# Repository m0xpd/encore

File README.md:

# encore!
An Echo/Delay Module for Eurorack, based on the PT2399

This repository describes a delay module, developed for electronic synthesisers, in Eurorack format, based on the [Princeton Technology](http://www.princeton.com.tw/en-us/products.aspx) [PT2399](http://www.princeton.com.tw/LinkClick.aspx?fileticket=XG0VYKi9QxE%3d&tabid=341&portalid=0&mid=828&language=en-US) device. 

**Functional Description**

A block diagram of  encore!  is shown below:

The module uses the PT2399 in an application environment derived from circuits in the [datasheet](http://www.princeton.com.tw/LinkClick.aspx?fileticket=XG0VYKi9QxE%3d&tabid=341&portalid=0&mid=828&language=en-US), but adds resources to enable patching and use in the Eurorack environment. 
These resources are described below.

In addition to the filtering already suggested in the application circuit and supported by the PT2399's integral amplifiers, encore! adds a 2nd order 
input filter and a 4th order output filter in Butterworth configuration. 

Unlike most simple PT2399 delay circuits, which are adjusted by potentiometers, encore! places the key parameters of Delay Length, Repeats (i.e. the gain 
of the recursion/feedback loop) and Level of the 'Wet' signal under voltage control, allowing parameter adjustment by potentiometers and/or CV inputs. 

In the case of the Delay Length, this is achieved by a Voltage Controlled Resistor circuit. 

In the case of the other two parameters, this is achieved by Voltage Controlled Amplifiers.  

Most significantly, encore! allows the user to patch external functions into the feedback/recursion loop that builds the echo (seen in the red dashed box in 
the block diagram above), using a loop send / return feature, which is mixed with the module's internal feedback path. This allows (e.g.) filters to be inserted 
to allow selective echos, multiple delay units to be cross-patched to build up complex echo strutures, etc..

**Licensing**

encore! is published under a Creative Commons BY-SA 4.0 [License](https://github.com/m0xpd/encore/blob/main/LICENSE.txt)

**Implementation**

The system is implemented on two PCBs; one for the main electronics and one for the controls and interface components.

The schematic for the main PCB is linked by the graphic below below (click for the full-size schematic):

I should have put a buffer between the PT2399 output filters and the input to the 'output filter' (which doesn't have a very high input impedance), but I 
didn't have any spare op-amp stages. I can live with the loading interactions as they are!

The schematic for the control PCB is linked below:

The two PCBs are joined electrically and mechanically by the 'Board interface', implemented as two 20-way headers (JP1 and JP2 in the schematics, male on the
 main board and female on the control board). A BoM for the main board is included.

You will find full details of the two printed circuit boards (in files for the Eagle Layout Editor) [here](https://github.com/m0xpd/encore/tree/main/PCBs) and 
a Kicad project defining a front panel [here](https://github.com/m0xpd/encore/tree/main/FrontPanel).

**Specifications**

encore! is 12HP wide and extends 38mm behind the front panel (when a standard Eurorack power header is inserted).

Caution: I've just been reminded (thanks Alex) that the PCBs of the present design overhang the left hand edge of the front panel by approximately 1mm. This 
is **an error on my part**, which I'll correct if ever there's a new 'edition' of encore! Multiple instances of encore! sit next to each other in a rack with 
no worries, but don't try to sit encore! next to a neighbour on its left which doesn't leave sufficient space.

encore! draws 36.5 mA from the +12V rail, 12.5 mA from the -12V rail, and nothing from the 5V rail.

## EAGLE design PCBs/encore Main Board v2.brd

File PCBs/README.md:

# Printed Circuit Boards

This folder contains details of the two PCBs required to implement the encore! delay module.

The PCB design files are presented in Eagle format.

Below you see a photo of the unpopulated PCBs.

The photo shows (left to right) the Main Board Component Side (Top), Main Board Bottom, Control Board Component Side (Top), and Control Board Bottom. 

Images of the main board on this repository are currently of a v1 protoype which included an error (a missing resistor), which is corrected in the design files.

## Main Board Capacitors 

The [BoM](https://github.com/m0xpd/encore/blob/main/PCBs/encore%20Main%20Board%20v2%20BoM.txt) is presented in the standard EAGLE format, which is verbose and not always helpful. A description of the capacitors used on the main board is given 
below (refer to the [schematic](https://user-images.githubusercontent.com/3152962/246648781-e0986f40-e248-4756-a811-1461d0e43b70.png) for component idents).

De-coupling capacitors C1, C2, C12, C13, C9, C20, C21 and modulate/de-modulate capacitors for the PT2399, C23, C24, C30, C32 (all having value quoted as 
“0.1u” in the BoM) are disc ceramics with 0.2-inch pitch.

Filter / coupling capacitors (C5, C7, C8, C14, C15, C16, C17, C18, C19, C25, C27, C28, C31, C33) are ceramics (for pF values), or multi-layer ceramics 
(for nF values), most of which have 0.1-inch pitch (except C7, C9, C27 & C33, where I used 0.2-inch pitch components for my own convenience). 

Polarized capacitors with 0.1-inch pitch are used for power supply smoothing (C3, C4, C10, C11), smoothing the mid-rail voltage of the PT2399 (C22) and 
d.c. blocking (C26, C29).

There is NO C6, due to an indexing error on my part.

## Control Board Components

Certain components on the control board have mechanical as well as electrical significance.

VR2 VR3 and VR4 are 9mm Vertical Alpha potentiometers [such as these](https://www.thonk.co.uk/shop/alpha-9mm-pots-vertical-t18/)

SK1:SK10 are [Thonkiconn](https://www.thonk.co.uk/shop/thonkiconn/) 3.5mm jack sockets

The combination of the alpha potentiometers and the Thonkiconn jacks gives the correct spacing between the Control Board and the Front Panel.

VR1 and VR5 are Song Huei 9mm Trim Pots, such as [these](https://www.thonk.co.uk/shop/ttpots/)

## Control Board 5V Power

5V is required on the Control Board for the derivation of control voltages via VR2:4 and the limiting of externally applied CVs via the Schottky diodes D1:6.

I did not want to use the PT2399's 5V supply in this application and found it convenient to generate 5V using a 78L05 regulator ("IC1") from the 12V rail, 
even though a much simpler circuit could have been used. Laziness rules! 

## Board Interface

Electrical and Mechanical Interface between the Main and Control Boards is achieved using 20-way 0.1-inch headers (JP1 & JP2). These are preferably a 
male component on the Main Board and a female component on the Control Board. I find it convenient to buy packs of 40-way headers and cut down to size.

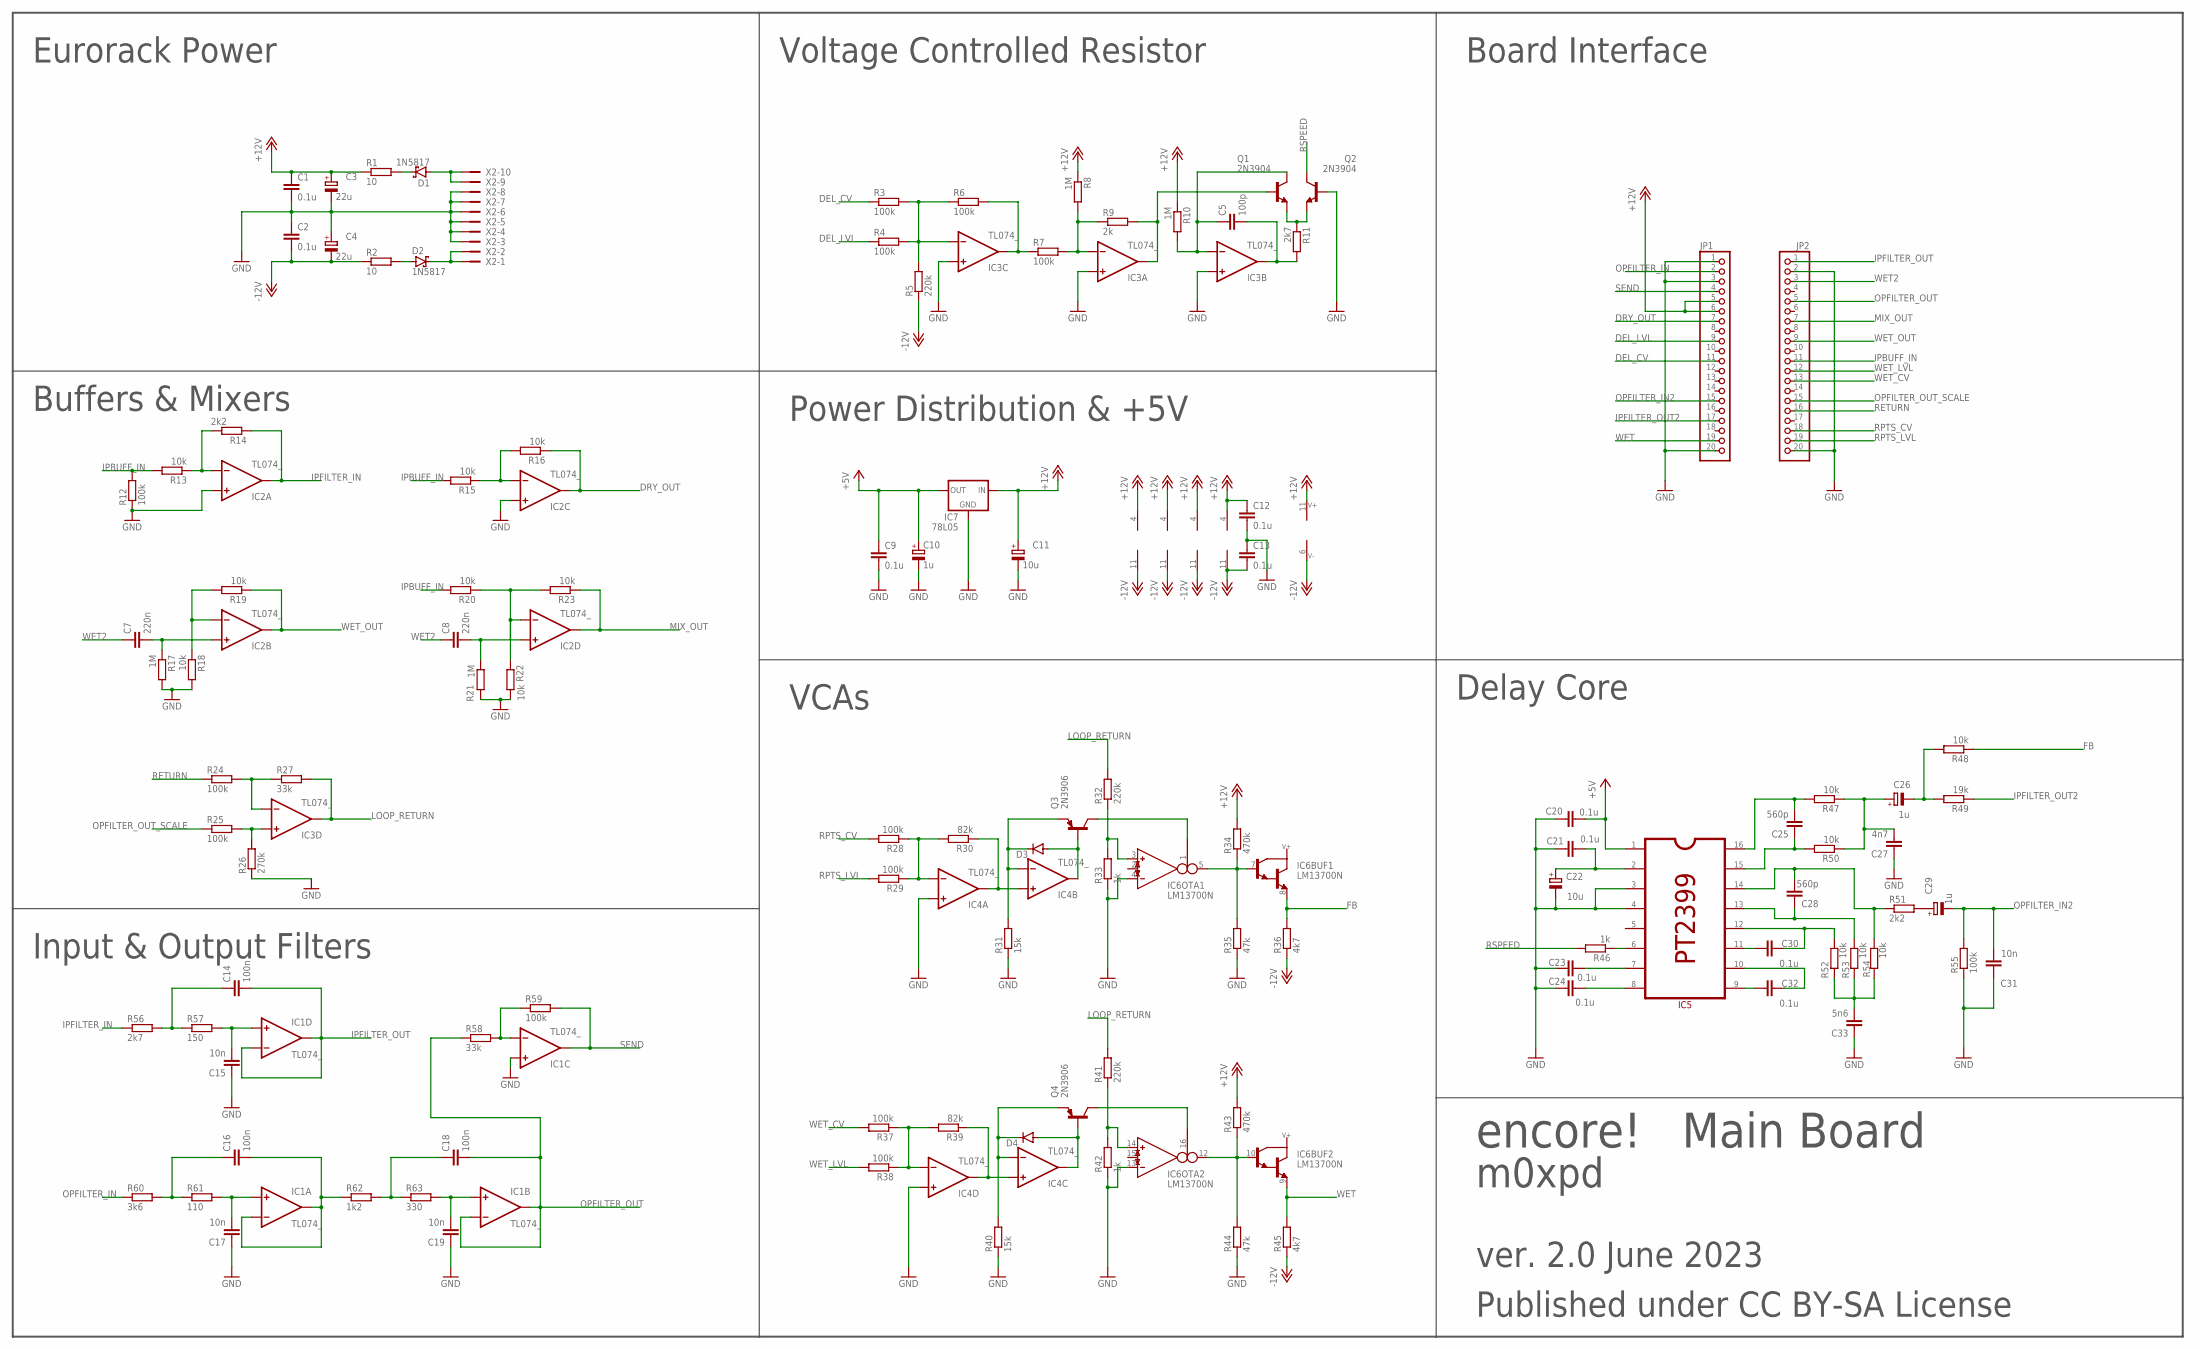
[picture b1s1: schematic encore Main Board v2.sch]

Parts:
C1, C2, C9, C12, C13, C20, C21, C23, C24, C30, C32: 0.1u; C050-025X075
C3, C4: 22u; E2,5-5
C5: 100p; C025-025X050
C7, C8: 220n; C050-024X044
C10, C26, C29: 1u; E2,5-5
C11, C22: 10u; E2,5-5
C14, C16, C18: 100n; C025-025X050
C15, C17, C19, C31: 10n; C025-025X050
C25, C28: 560p; C025-025X050
C27: 4n7; C050-025X075
C33: 5n6; C050-025X075
D1, D2: 1N5817; DO35-7
D3, D4: 1N4148DO35-7; DO35-7
IC1, IC2, IC3, IC4: TL074_; DIL14
IC5: PT2399; DIP-16
IC6: LM13700N; DIL16
IC7: 78L05; 78LXX
JP1, JP2: PINHD-1X20; 1X20
Q1, Q2: 2N3904; TO92
Q3, Q4: 2N3906; TO92
R1, R2: 10; 0204/7
R3, R4, R6, R7, R12, R24, R25, R28, R29, R37, R38, R55, R59: 100k; 0204/7
R5, R32, R41: 220k; 0204/7
R8, R10, R17, R21: 1M; 0204/7
R9: 2k; 0204/7
R11, R56: 2k7; 0204/7
R13, R15, R16, R18, R19, R20, R22, R23, R47, R48, R50, R52, R53, R54: 10k; 0204/7
R14, R51: 2k2; 0204/7
R26: 270k; 0204/7
R27, R58: 33k; 0204/7
R30, R39: 82k; 0204/7
R31, R40: 15k; 0204/7
R33, R42, R46: 1k; 0204/7
R34, R43: 470k; 0204/7
R35, R44: 47k; 0204/7
R36, R45: 4k7; 0204/7
R49: 19k; 0204/7
R57: 150; 0204/7
R60: 3k6; 0204/7
R61: 110; 0204/7
R62: 1k2; 0204/7
R63: 330; 0204/7
X2: 2510-; PAK100/2500-10

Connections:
+5V: C9.1, C10.+, C20.2, IC5.1, IC7.OUT
+12V: C1.1, C3.+, C11.+, C12.1, IC1.4 (V+), IC2.4 (V+), IC3.4 (V+), IC4.4 (V+), IC6.11 (V+), IC7.IN, JP1.5, JP1.6, R1.1, R8.1, R10.1, R34.2, R43.2
-12V: C2.2, C4.-, C13.2, IC1.11 (V-), IC2.11 (V-), IC3.11 (V-), IC4.11 (V-), IC6.6 (V-), R2.1, R5.1, R36.1, R45.1
DEL_CV: JP1.11, R3.1
DEL_LVL: JP1.9, R4.1
DRY_OUT: IC2.8 (OUT), JP1.7, R16.1
FB: IC6.8 (E), R36.2, R48.1
GND: C1.2, C2.1, C3.-, C4.+, C9.2, C10.-, C11.-, C12.2, C13.1, C15.1, C17.1, C19.1, C20.1, C21.1, C22.-, C23.1, C24.1, C27.1, C31.1, C33.1, IC1.10 (+IN), IC2.3 (+IN), IC2.10 (+IN), IC3.3 (+IN), IC3.5 (+IN), IC3.10 (+IN), IC4.3 (+IN), IC4.12 (+IN), IC5.3, IC5.4, IC6.4 (IN_N), IC6.13 (IN_N), IC7.GND, JP1.1, JP1.3, JP1.20, JP2.2, JP2.20, Q2.2 (B), R12.1, R17.2, R18.2, R21.2, R22.2, R26.1, R31.1, R33.1, R35.1, R40.1, R42.1, R44.1, R55.1, X2.3, X2.4, X2.5, X2.6, X2.7, X2.8
IPBUFF_IN: JP2.11, R12.2, R13.2, R15.2, R20.2
IPFILTER_IN: IC2.1 (OUT), R14.1, R56.1
IPFILTER_OUT: C14.2, IC1.13 (-IN), IC1.14 (OUT), JP2.1
IPFILTER_OUT2: JP1.17, R49.1
LOOP_RETURN: IC3.14 (OUT), R27.2, R32.2, R41.2
MIX_OUT: IC2.14 (OUT), JP2.7, R23.1
unnamed: IC3.1 (OUT), Q1.2 (B), R9.2
unnamed: C15.2, IC1.12 (+IN), R57.2
unnamed: C5.1, IC3.6 (-IN), Q1.1 (C), R10.2
unnamed: C14.1, R56.2, R57.1
unnamed: C16.2, IC1.1 (OUT), IC1.2 (-IN), R62.1
unnamed: C16.1, R60.2, R61.1
unnamed: C17.2, IC1.3 (+IN), R61.2
unnamed: C5.2, IC3.7 (OUT), R11.2
unnamed: Q1.3 (E), Q2.3 (E), R11.1
unnamed: C18.1, R62.2, R63.1
unnamed: C19.2, IC1.5 (+IN), R63.2
unnamed: IC2.2 (-IN), R13.1, R14.2
unnamed: D1.A, X2.9, X2.10
unnamed: D1.C, R1.2
unnamed: C26.-, R48.2, R49.2
unnamed: IC2.6 (-IN), R18.1, R19.2
unnamed: C21.2, C22.+, IC5.2
unnamed: IC1.9 (-IN), R58.2, R59.1
unnamed: IC6.5 (OUT), IC6.7 (B), R34.1, R35.2
unnamed: C7.2, IC2.5 (+IN), R17.1
unnamed: IC3.12 (+IN), R25.2, R26.2
unnamed: C32.2, IC5.10
unnamed: IC6.3 (IN_P), R32.1, R33.2
unnamed: D3.A, IC4.7 (OUT), Q3.2 (B)
unnamed: D3.C, IC4.6 (-IN), Q3.3 (E), R31.2
unnamed: D2.A, R2.2
unnamed: D2.C, X2.1, X2.2
unnamed: IC6.1 (I_BIAS), Q3.1 (C)
unnamed: IC4.1 (OUT), IC4.5 (+IN), R30.1
unnamed: IC5.6, R46.1
unnamed: IC4.2 (-IN), R28.1, R29.1, R30.2
unnamed: IC4.10 (+IN), IC4.14 (OUT), R39.1
unnamed: IC6.10 (B), IC6.12 (OUT), R43.1, R44.2
unnamed: IC6.16 (I_BIAS), Q4.1 (C)
unnamed: IC6.14 (IN_P), R41.1, R42.2
unnamed: D4.C, IC4.9 (-IN), Q4.3 (E), R40.2
unnamed: D4.A, IC4.8 (OUT), Q4.2 (B)
unnamed: IC3.2 (-IN), R7.2, R8.2, R9.1
unnamed: IC4.13 (-IN), R37.1, R38.1, R39.2
unnamed: IC3.8 (OUT), R6.2, R7.1
unnamed: C23.2, IC5.7
unnamed: IC3.9 (-IN), R3.2, R4.2, R5.2, R6.1
unnamed: C24.2, IC5.8
unnamed: C25.2, IC5.16, R47.2
unnamed: C25.1, IC5.15, R50.2
unnamed: C26.+, C27.2, R47.1, R50.1
unnamed: C32.1, IC5.9
unnamed: C28.2, IC5.14, R51.1, R54.1
unnamed: C28.1, IC5.13, R53.1
unnamed: C30.1, IC5.11
unnamed: C30.2, IC5.12, R52.1
unnamed: C33.2, R52.2, R53.2, R54.2
unnamed: C29.+, R51.2
unnamed: C8.2, IC2.12 (+IN), R21.1
unnamed: IC2.13 (-IN), R20.1, R22.1, R23.2
unnamed: IC3.13 (-IN), R24.2, R27.1
unnamed: IC2.9 (-IN), R15.1, R16.2
OPFILTER_IN: JP1.2, R60.1
OPFILTER_IN2: C29.-, C31.2, JP1.15, R55.2
OPFILTER_OUT: C18.2, IC1.6 (-IN), IC1.7 (OUT), JP2.5, R58.1
OPFILTER_OUT_SCALE: JP2.15, R25.1
RETURN: JP2.16, R24.1
RPTS_CV: JP2.18, R28.2
RPTS_LVL: JP2.19, R29.2
RSPEED: Q2.1 (C), R46.2
SEND: IC1.8 (OUT), JP1.4, R59.2
WET: IC6.9 (E), JP1.19, R45.2
WET2: C7.1, C8.1, JP2.3
WET_CV: JP2.13, R37.2
WET_LVL: JP2.12, R38.2
WET_OUT: IC2.7 (OUT), JP2.9, R19.1

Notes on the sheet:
encore! Main Board
m0xpd
ver. 2.0 June 2023
Eurorack Power
Input & Output Filters
Buffers & Mixers
VCAs
Voltage Controlled Resistor
Power Distribution & +5V
Board Interface
Delay Core
Published under CC BY-SA License

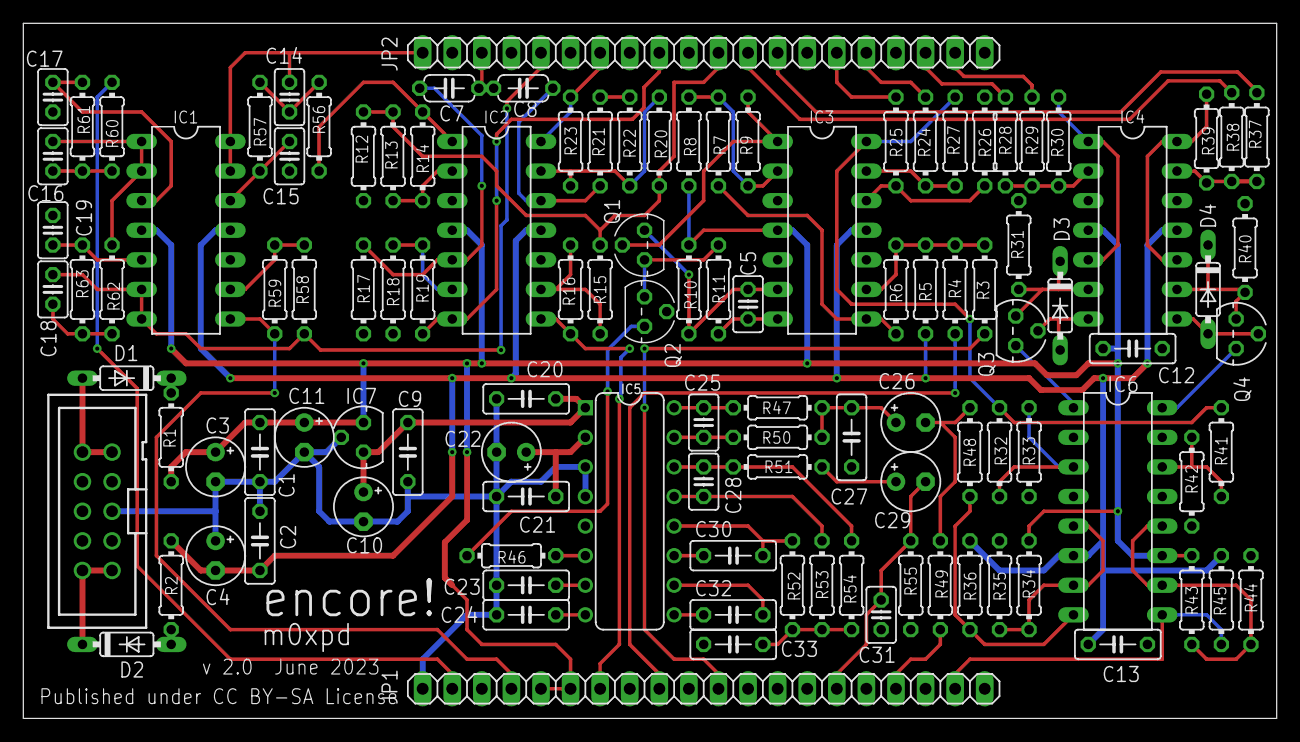
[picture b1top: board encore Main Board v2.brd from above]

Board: 2 copper layers, 107.6 x 59.7 mm, 113 parts (0 on the bottom side), 85 nets.

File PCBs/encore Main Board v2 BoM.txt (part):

Partlist exported from /Users/pauldarlington/Documents/EAGLE/projects/Delay/encore Main Board v2.sch at 18/06/2023 05:13

Part Value        Device               Package        Description                          MF MPN         OC_FARNELL OC_NEWARK POPULARITY SPICEPREFIX
C1   0.1u         C-EU050-025X075      C050-025X075   CAPACITOR, European symbol                                               29         C          
C2   0.1u         C-EU050-025X075      C050-025X075   CAPACITOR, European symbol                                               29         C          
C3   22u          CPOL-EUE2.5-5        E2,5-5         POLARIZED CAPACITOR, European symbol                                     16         C          
C4   22u          CPOL-EUE2.5-5        E2,5-5         POLARIZED CAPACITOR, European symbol                                     16         C          
C5   100p         C-EU025-025X050      C025-025X050   CAPACITOR, European symbol                                               65         C          
C7   220n         C-EU050-024X044      C050-024X044   CAPACITOR, European symbol                                               33         C          
C8   220n         C-EU050-024X044      C050-024X044   CAPACITOR, European symbol                                               33         C          
C9   0.1u         C-EU050-025X075      C050-025X075   CAPACITOR, European symbol                                               29         C          
C10  1u           CPOL-EUE2.5-5        E2,5-5         POLARIZED CAPACITOR, European symbol                                     16         C          
C11  10u          CPOL-EUE2.5-5        E2,5-5         POLARIZED CAPACITOR, European symbol                                     16         C          
C12  0.1u         C-EU050-025X075      C050-025X075   CAPACITOR, European symbol                                               29         C          
C13  0.1u         C-EU050-025X075      C050-025X075   CAPACITOR, European symbol                                               29         C          
C14  100n         C-EU025-025X050      C025-025X050   CAPACITOR, European symbol                                               65         C          
C15  10n          C-EU025-025X050      C025-025X050   CAPACITOR, European symbol                                               65         C          
C16  100n         C-EU025-025X050      C025-025X050   CAPACITOR, European symbol                                               65         C          
C17  10n          C-EU025-025X050      C025-025X050   CAPACITOR, European symbol                                               65         C          
C18  100n         C-EU025-025X050      C025-025X050   CAPACITOR, European symbol                                               65         C          
C19  10n          C-EU025-025X050      C025-025X050   CAPACITOR, European symbol                                               65         C          
C20  0.1u         C-EU050-025X075      C050-025X075   CAPACITOR, European symbol                                               29         C          
C21  0.1u         C-EU050-025X075      C050-025X075   CAPACITOR, European symbol                                               29         C          
C22  10u          CPOL-EUE2.5-5        E2,5-5         POLARIZED CAPACITOR, European symbol                                     16         C          
C23  0.1u         C-EU050-025X075      C050-025X075   CAPACITOR, European symbol                                               29         C          
C24  0.1u         C-EU050-025X075      C050-025X075   CAPACITOR, European symbol                                               29         C          
C25  560p         C-EU025-025X050      C025-025X050   CAPACITOR, European symbol                                               65         C          
C26  1u           CPOL-EUE2.5-5        E2,5-5         POLARIZED CAPACITOR, European symbol                                     16         C          
C27  4n7          C-EU050-025X075      C050-025X075   CAPACITOR, European symbol                                               29         C          
C28  560p         C-EU025-025X050      C025-025X050   CAPACITOR, European symbol                                               65         C          
C29  1u           CPOL-EUE2.5-5        E2,5-5         POLARIZED CAPACITOR, European symbol                                     16         C          
C30  0.1u         C-EU050-025X075      C050-025X075   CAPACITOR, European symbol                                               29         C          
C31  10n          C-EU025-025X050      C025-025X050   CAPACITOR, European symbol                                               65         C          
C32  0.1u         C-EU050-025X075      C050-025X075   CAPACITOR, European symbol                                               29         C          
C33  5n6          C-EU050-025X075      C050-025X075   CAPACITOR, European symbol                                               29         C          
D1   1N5817       SCHOTTKY-DIODEDO35-7 DO35-7         Schottky Diode                                                           3                     
D2   1N5817       SCHOTTKY-DIODEDO35-7 DO35-7         Schottky Diode                                                           3                     
D3   1N4148DO35-7 1N4148DO35-7         DO35-7         DIODE                                                                    58                    
D4   1N4148DO35-7 1N4148DO35-7         DO35-7         DIODE                                                                    58                    
IC1  TL074_       TL074_               DIL14          Generic Quad Op Amp                                                                            
IC2  TL074_       TL074_               DIL14          Generic Quad Op Amp                                                                            
IC3  TL074_       TL074_               DIL14          Generic Quad Op Amp                                                                            
IC4  TL074_       TL074_               DIL14          Generic Quad Op Amp                                                                            
IC5  PT2399       PT2399               DIP-16                                                                                                        
IC6  LM13700N     LM13700N             DIL16          Dual OTA with buffers                                                                          
IC7  78L05        78LXX                78LXX          VOLTAGE REGULATOR                                                        6                     
JP1               PINHD-1X20           1X20           PIN HEADER                                                               6                     
JP2               PINHD-1X20           1X20           PIN HEADER                                                               6                     
Q1   2N3904       2N3904               TO92           NPN Transistor                                                           0                     
Q2   2N3904       2N3904               TO92           NPN Transistor                                                           0                     
Q3   2N3906       2N3906               TO92           PNP Transistor                                                           11                    
Q4   2N3906       2N3906               TO92           PNP Transistor                                                           11                    
R1   10           R-EU_0204/7          0204/7         RESISTOR, European symbol                                                79         R          
R2   10           R-EU_0204/7          0204/7         RESISTOR, European symbol                                                79         R          
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
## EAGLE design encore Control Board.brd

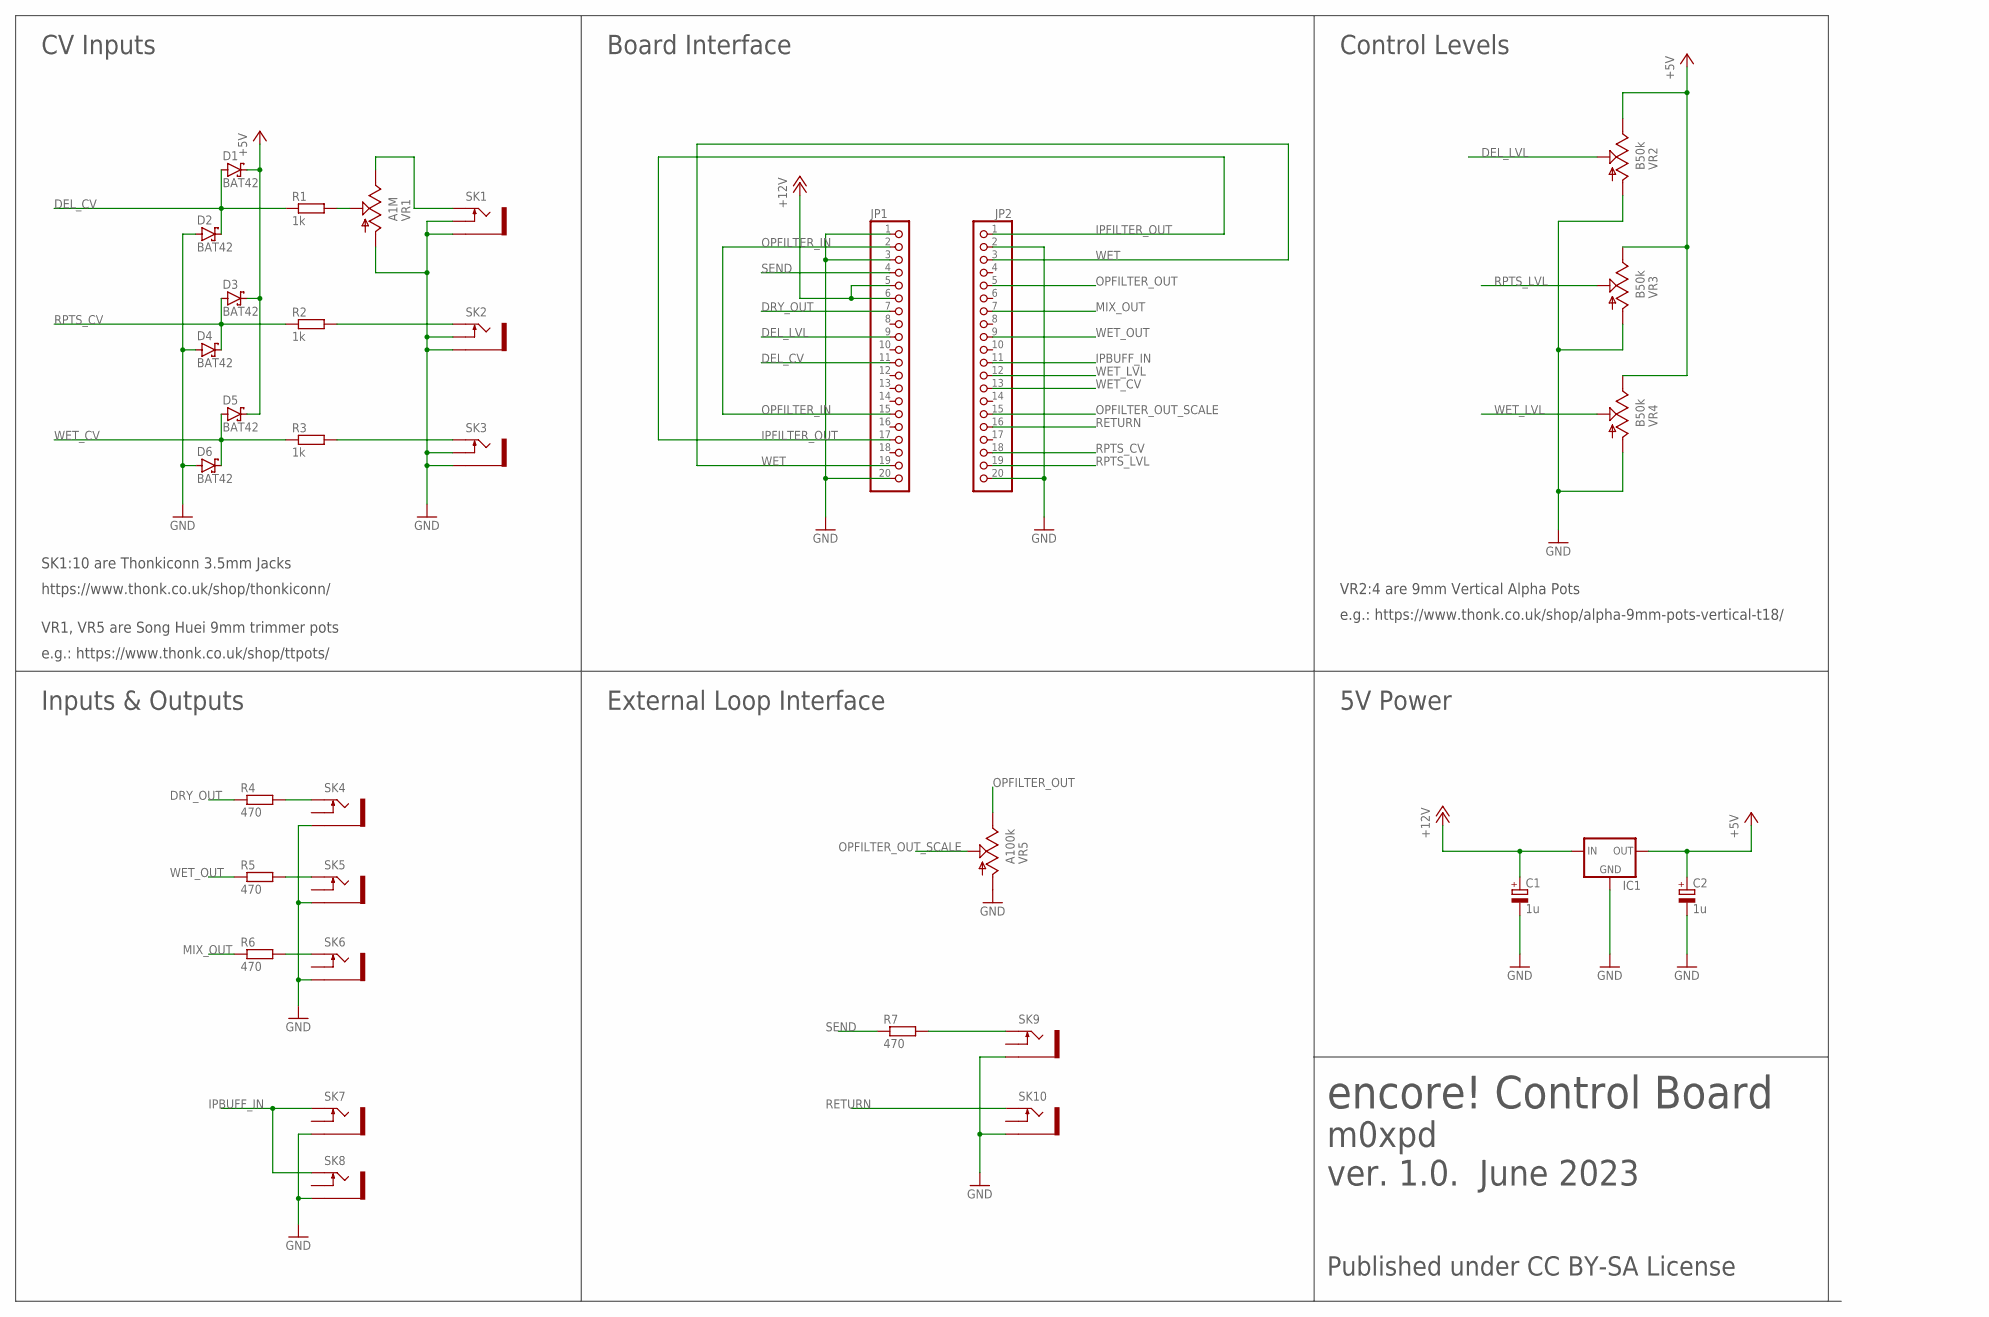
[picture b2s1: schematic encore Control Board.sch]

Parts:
C1, C2: 1u; E2,5-5
D1, D2, D3, D4, D5, D6: BAT42; DO35-10
IC1: 78LXX
JP1, JP2: PINHD-1X20; 1X20
R1, R2, R3: 1k; 0204/7
R4, R5, R6, R7: 470; 0204/7
SK1, SK2, SK3, SK4, SK5, SK6, SK7, SK8, SK9, SK10: THONKICONN_JACK; WQP-PJ301M-12_JACK
VR1: A1M; 9MM_SNAP-IN_POT
VR2, VR3, VR4: B50k; 9MM_SNAP-IN_POT
VR5: A100k; 9MM_SNAP-IN_POT

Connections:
+5V: C2.+, D1.C, D3.C, D5.C, IC1.OUT, VR2.3 (E), VR3.3 (E), VR4.3 (E)
+12V: C1.+, IC1.IN, JP1.5, JP1.6
DEL_CV: D1.A, D2.C, JP1.11, R1.1
DEL_LVL: JP1.9, VR2.2 (S)
DRY_OUT: JP1.7, R4.1
GND: C1.-, C2.-, D2.A, D4.A, D6.A, IC1.GND, JP1.1, JP1.3, JP1.20, JP2.2, JP2.20, SK1.P$2_SWITCH (SWITCH), SK1.P$3_SLEEVE (SLEEVE), SK2.P$2_SWITCH (SWITCH), SK2.P$3_SLEEVE (SLEEVE), SK3.P$2_SWITCH (SWITCH), SK3.P$3_SLEEVE (SLEEVE), SK4.P$3_SLEEVE (SLEEVE), SK5.P$3_SLEEVE (SLEEVE), SK6.P$3_SLEEVE (SLEEVE), SK7.P$3_SLEEVE (SLEEVE), SK8.P$3_SLEEVE (SLEEVE), SK9.P$3_SLEEVE (SLEEVE), SK10.P$3_SLEEVE (SLEEVE), VR1.1 (A), VR2.1 (A), VR3.1 (A), VR4.1 (A), VR5.1 (A)
IPBUFF_IN: JP2.11, SK7.P$1_TIP (TIP), SK8.P$1_TIP (TIP)
IPFILTER_OUT: JP1.17, JP2.1
MIX_OUT: JP2.7, R6.1
unnamed: R4.2, SK4.P$1_TIP (TIP)
unnamed: R5.2, SK5.P$1_TIP (TIP)
unnamed: R6.2, SK6.P$1_TIP (TIP)
unnamed: R7.2, SK9.P$1_TIP (TIP)
unnamed: SK1.P$1_TIP (TIP), VR1.3 (E)
unnamed: R2.2, SK2.P$1_TIP (TIP)
unnamed: R3.2, SK3.P$1_TIP (TIP)
unnamed: R1.2, VR1.2 (S)
OPFILTER_IN: JP1.2, JP1.15
OPFILTER_OUT: JP2.5, VR5.3 (E)
OPFILTER_OUT_SCALE: JP2.15, VR5.2 (S)
RETURN: JP2.16, SK10.P$1_TIP (TIP)
RPTS_CV: D3.A, D4.C, JP2.18, R2.1
RPTS_LVL: JP2.19, VR3.2 (S)
SEND: JP1.4, R7.1
WET: JP1.19, JP2.3
WET_CV: D5.A, D6.C, JP2.13, R3.1
WET_LVL: JP2.12, VR4.2 (S)
WET_OUT: JP2.9, R5.1

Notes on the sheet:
encore! Control Board
m0xpd
ver. 1.0. June 2023
Published under CC BY-SA License
CV Inputs
Board Interface
Control Levels
Inputs & Outputs
External Loop Interface
5V Power
VR2:4 are 9mm Vertical Alpha Pots
e.g.: https://www.thonk.co.uk/shop/alpha-9mm-pots-vertical-t18/
SK1:10 are Thonkiconn 3.5mm Jacks
https://www.thonk.co.uk/shop/thonkiconn/
VR1, VR5 are Song Huei 9mm trimmer pots
e.g.: https://www.thonk.co.uk/shop/ttpots/

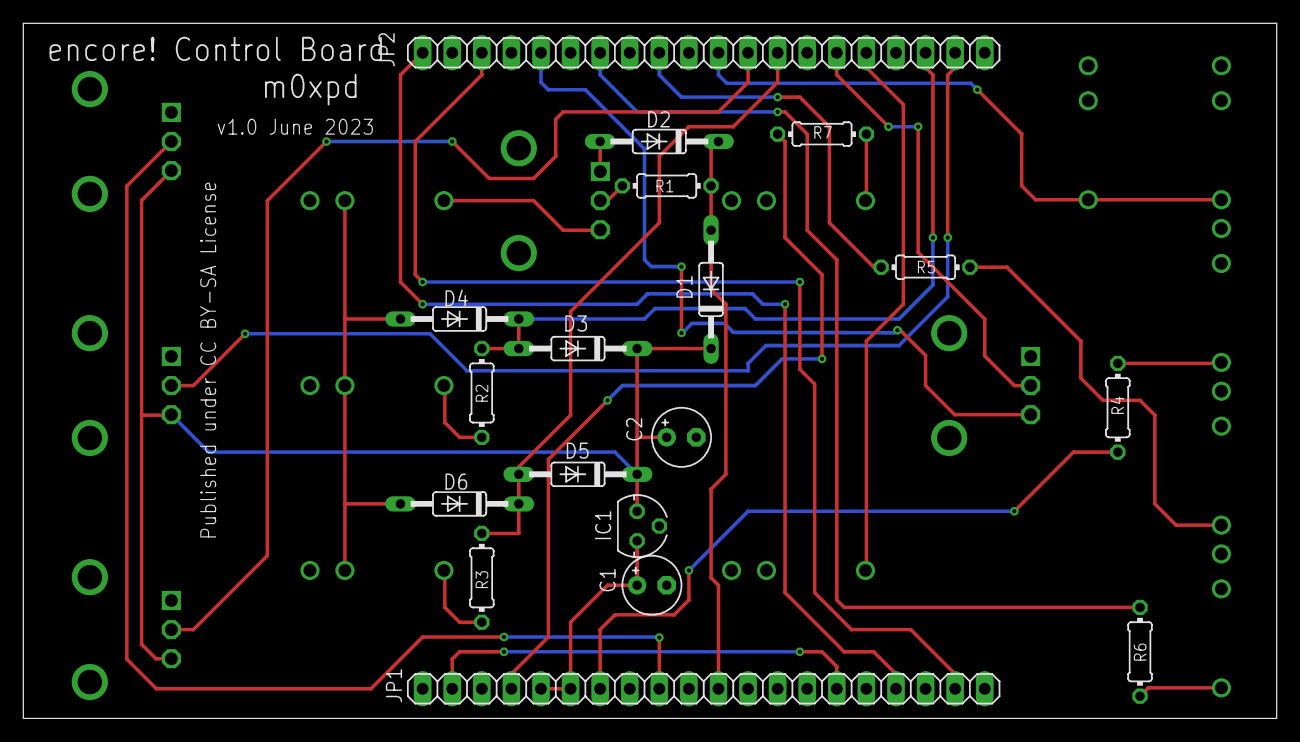
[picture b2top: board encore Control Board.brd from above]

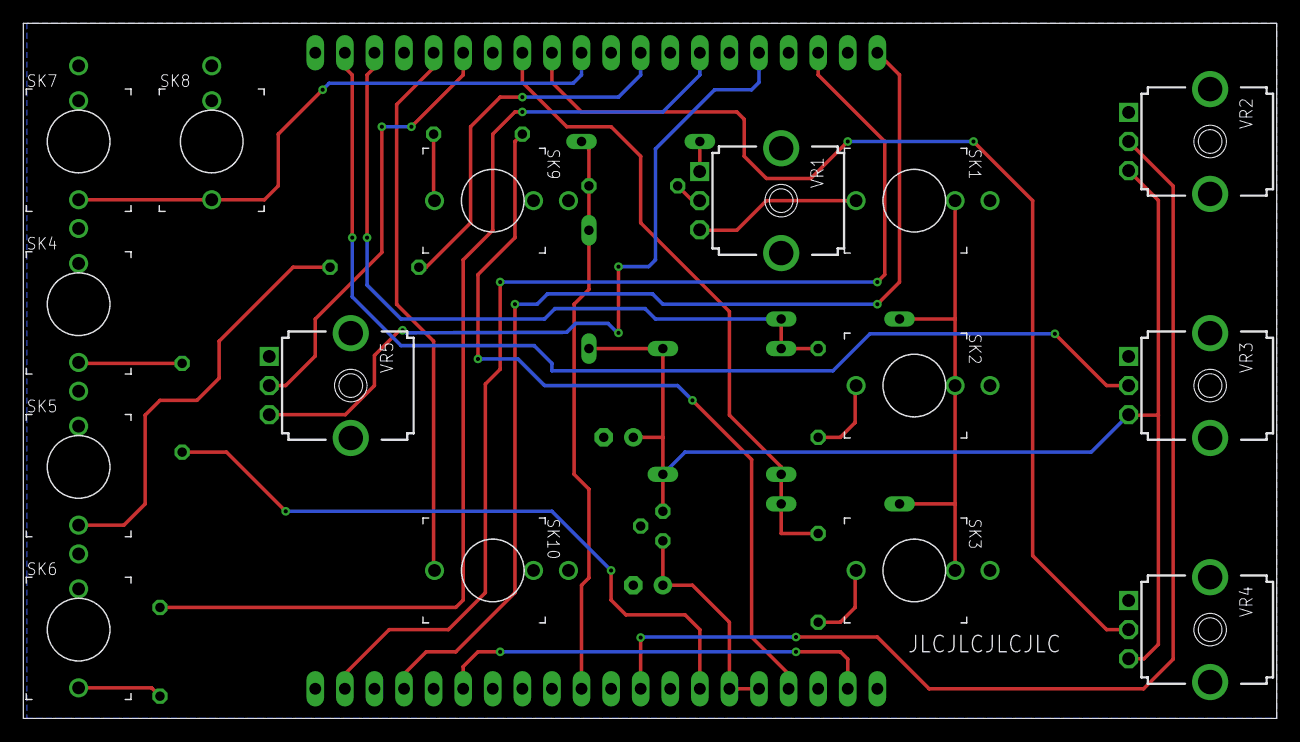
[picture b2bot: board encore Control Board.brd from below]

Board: 2 copper layers, 107.6 x 59.7 mm, 33 parts (15 on the bottom side), 28 nets.

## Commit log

2023-06-06 Rename encore Control Board.brd to PCBs/encore Control Board.brd
2023-06-06 Rename encore.kicad_pcb to FrontPanel/encore.kicad_pcb
2023-06-06 Rename encore Control Board.sch to PCBs/encore Control Board.sch
2023-06-06 Rename encore Main Board.brd to PCBs/encore Main Board.brd
2023-06-06 Rename encore Main Board.sch to PCBs/encore Main Board.sch
2023-06-06 Rename encore.kicad_pro to FrontPanel/encore.kicad_pro
2023-06-06 Rename encore.kicad_sch to FrontPanel/encore.kicad_sch
2023-06-18 Rename PCBs/encore Main Board.sch to PCBs/Faulty_v1/encore Main Board.sch
2023-06-18 Rename PCBs/encore Main Board.brd to PCBs/Faulty_v1/encore Main Board.brd
